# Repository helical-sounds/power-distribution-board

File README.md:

# Power Distribution Board

## Description

## Contact

Drop me an email at guy@rumblesan.com

## License

BSD License.

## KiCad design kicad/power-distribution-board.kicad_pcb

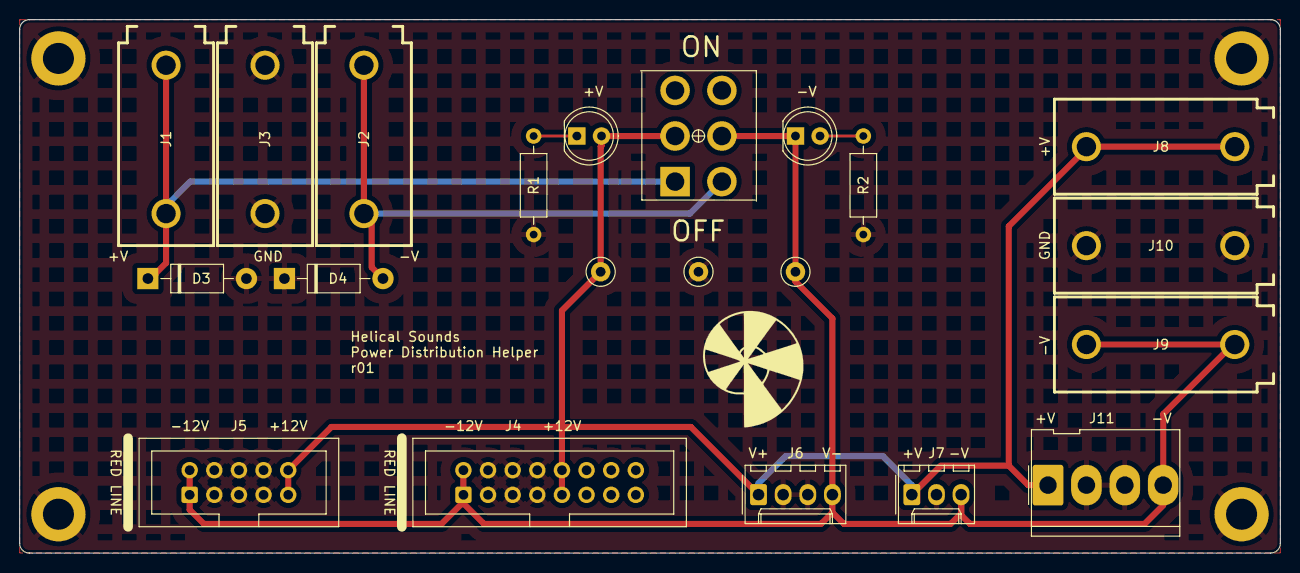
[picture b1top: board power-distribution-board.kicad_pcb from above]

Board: 2 copper layers, 130.0 x 55.0 mm, 25 parts (0 on the bottom side), 7 nets.

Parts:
D1, D2: LED; LED_D5.0mm
D3, D4: 1N4001; D_DO-41_SOD81_P10.16mm_Horizontal
H1, H2, H3, H4: MountingHole_Pad; MountingHole_3.2mm_M3_DIN965_Pad
J1, J2, J3, J8, J9, J10: Banana Socket PCBMount; Deltron_571_PCB_BananaJack
J4: Conn_02x08_Odd_Even; Eurorack_Power_IDC-Header_2x08_P2.54mm_Vertical
J5: Conn_02x05_Odd_Even; Eurorack_Power_IDC-Header_2x05_P2.54mm_Vertical
J6: 4U_Power; 4u_Power_Molex_KK-254_22-27-2041_1x04_P2.54mm_Vertical
J7: Conn_01x03; Molex_KK-254_AE-6410-03A_1x03_P2.54mm_Vertical
J11: Conn_01x04; Molex_KK-396_5273-04A_1x04_P3.96mm_Vertical
R1, R2: 2k2; R_Axial_DIN0207_L6.3mm_D2.5mm_P10.16mm_Horizontal
SW1: SW_DPDT_x2; SW_DPDT_DailyWell_MiniToggle
TP1, TP2, TP3: TestPoint; TestPoint_Loop_D2.50mm_Drill1.0mm_LowProfile

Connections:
+12V: D1.2 (A), J4.9 (+12V), J4.10 (+12V), J5.9 (+12V), J5.10 (+12V), J6.1 (+12V), J7.1, J8.1, J11.1, SW1.2 (B), TP1.1
-12V: D2.1 (K), J4.1 (-12V), J4.2 (-12V), J5.1 (-12V), J5.2 (-12V), J6.4 (-12V), J7.3, J9.1, J11.4, SW1.5 (B), TP2.1
GND: D3.2 (A), D4.1 (K), H1.1, H2.1, H3.1, H4.1, J3.1, J4.3 (GND), J4.4 (GND), J4.5 (GND), J4.6 (GND), J4.7 (GND), J4.8 (GND), J5.3 (GND), J5.4 (GND), J5.5 (GND), J5.6 (GND), J5.7 (GND), J5.8 (GND), J6.2 (GND), J6.3 (GND), J7.2, J10.1, J11.2, J11.3, R1.2, R2.2, TP3.1
unnamed: D1.1 (K), R1.1
unnamed: D2.2 (A), R2.1
unnamed: D3.1 (K), J1.1, SW1.1 (A)
unnamed: D4.2 (A), J2.1, SW1.4 (A)

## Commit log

2025-02-11 Adding pcb layout
2025-02-13 Tweaking layout and adding silkscreen text
2025-02-13 Create gerbers

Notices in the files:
kicad/power-distribution-board.kicad_pcb:
creativecommons.org/licenses/by/4.0
License: CC BY 4.0
